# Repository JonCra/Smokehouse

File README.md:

# Project Smokehouse - RCET Project (Fall 2026 Semester)
## Continuation of [Project BLOODHOUND](https://github.com/rc-earnest/BloodHound)
### Smokehouse Contributors (Fall 2026 Semester)
<dl>
<dt>Micah Spencer - Project Lead, 6th Semester RCET Student</dt>
<dd>Redesign and improvement of drive controller(s) and addition of semi-permanent peripheral data collection</dd>
<dt>Jonas Cram - Project Lead, 6th Semester RCET Student</dt>
<dd>Design and construction of "control/base station" for remote operations</dd>
</dl>

### BLOODHOUND Contributors (Spring 2026 Semester)
<dl>
<dt>Noah Holloway - Project Lead, 6th Semester RCET Student</dt>
<dd>ATV steering/driving controls and physical/electrical hardware</dd>
<dt>Rudy Earnest - Project Lead, 6th Semester RCET Student</dt>
<dd>Pan-Tilt-Zoom (PTZ) Cameras and other peripherals</dd>
<dt>Micah Spencer - Project Assistant, 5th Semester RCET Student</dt>
<dd>Real-Time Kinematics (RTK)/GPS Module</dd>
<dt>Jonas Cram - Project Assistant, 5th Semester RCET Student</dt>
<dd>Light Detection and Ranging (LiDAR) Module</dd>

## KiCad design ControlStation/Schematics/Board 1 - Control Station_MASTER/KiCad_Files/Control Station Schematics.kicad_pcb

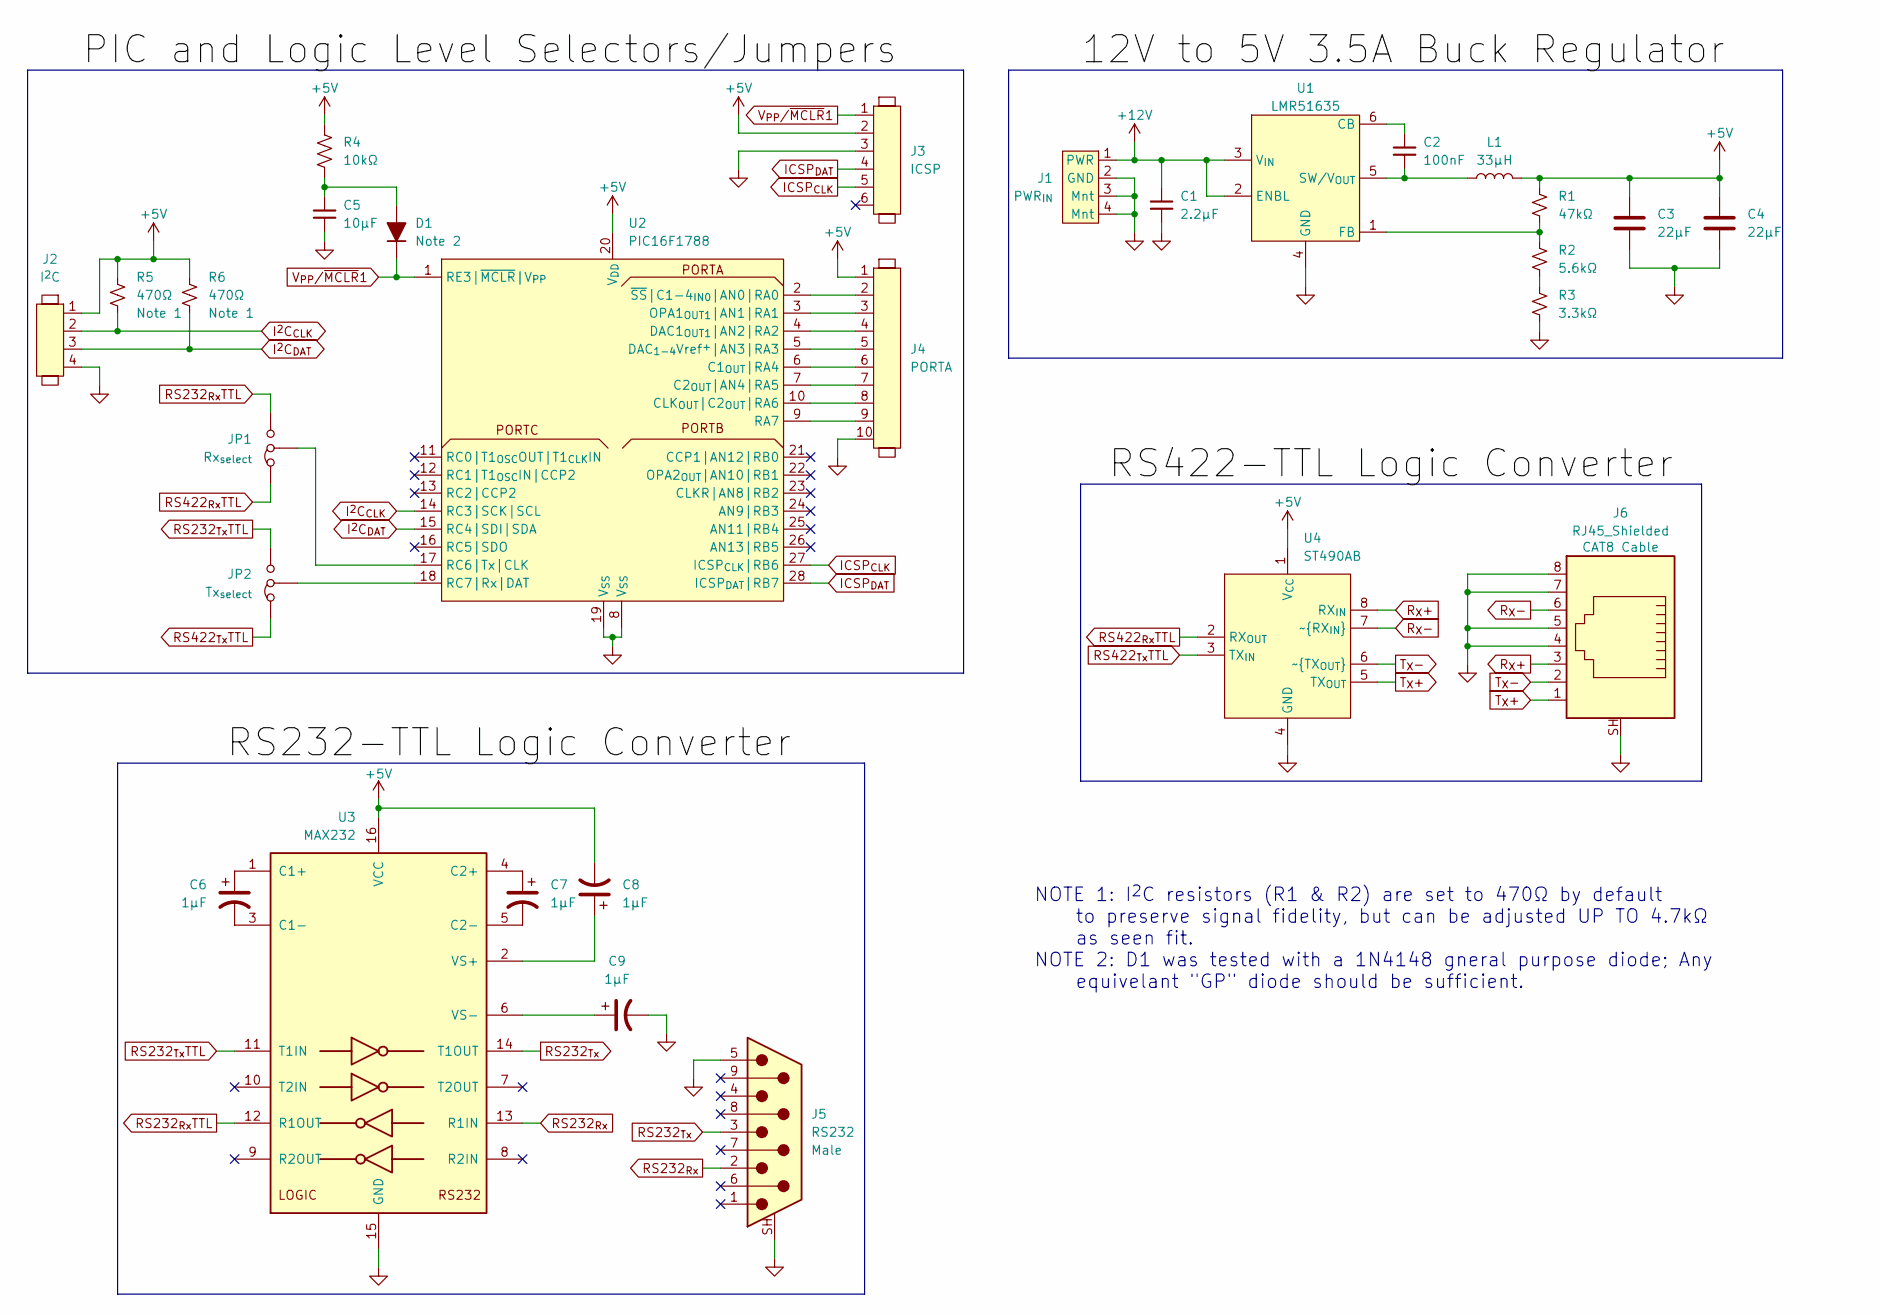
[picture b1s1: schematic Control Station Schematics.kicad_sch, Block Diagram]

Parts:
C1: 2.2μF; C_0805_2012Metric_Pad1.18x1.45mm_HandSolder
C2: 100nF; C_0805_2012Metric_Pad1.18x1.45mm_HandSolder
C3, C4: 22μF; C_0805_2012Metric_Pad1.18x1.45mm_HandSolder
C5: 10μF; C_0805_2012Metric_Pad1.18x1.45mm_HandSolder
C6, C7, C8, C9: 1μF; C_0805_2012Metric_Pad1.18x1.45mm_HandSolder
D1: D_0805_2012Metric_Pad1.15x1.40mm_HandSolder
J1: PWR_{IN}; XT30PW-M
J2: I^{2}C; Molex_Micro-Fit_3.0_43045-0400_2x02_P3.00mm_Horizontal
J3: ICSP; PinHeader_1x06_P1.00mm_Vertical
J4: PORTA; Molex_Micro-Fit_3.0_43045-1010_2x05-1MP_P3.00mm_Horizontal
J5: RS232; DSUB-9_Socket_Horizontal_P2.77x2.84mm_EdgePinOffset7.70mm_H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
J6: RJ45_Shielded; CONN8_406541_TEC
JP1: Rx_{select}; PinHeader_1x03_P1.00mm_Vertical
JP2: Tx_{select}; PinHeader_1x03_P1.00mm_Vertical
L1: 33μH; L_Bourns_SRP7028A_7.3x6.6mm
R1: 47kΩ; R_0805_2012Metric_Pad1.20x1.40mm_HandSolder
R2: 5.6kΩ; R_0805_2012Metric_Pad1.20x1.40mm_HandSolder
R3: 3.3kΩ; R_0805_2012Metric_Pad1.20x1.40mm_HandSolder
R4: 10kΩ; R_0805_2012Metric_Pad1.20x1.40mm_HandSolder
R5, R6: 470Ω; R_0805_2012Metric_Pad1.20x1.40mm_HandSolder
U1: LMR51635; DDC0006A-MFG
U2: PIC16F1788; SSOP-28
U3: MAX232; SOP-16_4.55x10.3mm_P1.27mm
U4: ST490AB; SO-8_3.9x4.9mm_P1.27mm

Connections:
+12V: C1.1, J1.1 (PWR), U1.2 (ENBL), U1.3 (V_{IN})
GND: C1.2, C3.2, C4.2, C5.2, C9.2, J1.2 (GND), J1.3 (Mnt), J1.4 (Mnt), J2.4, J3.3, J4.10, J5.5, J5.SH (PAD), J6.4, J6.5, J6.7, J6.8, J6.SH, R3.2, U1.4 (GND), U2.8 (V_{SS}), U2.19 (V_{SS}), U3.15 (GND), U4.4 (GND)
ICSP_{CLK}: J3.5, U2.27 (ICSP_{CLK}|RB6)
ICSP_{DAT}: J3.4, U2.28 (ICSP_{DAT}|RB7)
I^{2}C_{CLK}: J2.2, R5.2, U2.14 (RC3|SCK|SCL)
I^{2}C_{DAT}: J2.3, R6.2, U2.15 (RC4|SDI|SDA)
unnamed: C5.1, D1.2 (A), R4.2
unnamed: JP1.2 (C), U2.17 (RC6|Tx|CLK)
unnamed: JP2.2 (C), U2.18 (RC7|Rx|DAT)
unnamed: R2.2, R3.1
unnamed: C2.1, U1.6 (CB)
unnamed: R1.2, R2.1, U1.1 (FB)
unnamed: C2.2, L1.1, U1.5 (SW/V_{OUT})
unnamed: J4.6, U2.6 (C1_{OUT}|RA4)
unnamed: J4.7, U2.7 (C2_{OUT}|AN4|RA5)
unnamed: J4.8, U2.10 (CLK_{OUT}|C2_{OUT}|RA6)
unnamed: J4.4, U2.4 (DAC1_{OUT1}|AN2|RA2)
unnamed: J4.5, U2.5 (DAC_{1-4}Vref^{+}|AN3|RA3)
unnamed: J4.3, U2.3 (OPA1_{OUT1}|AN1|RA1)
unnamed: J4.9, U2.9 (RA7)
unnamed: J4.2, U2.2 (~SS|C1-4_{IN0}|AN0|RA0)
unnamed: C6.1, U3.1 (C1+)
unnamed: C6.2, U3.3 (C1-)
unnamed: C7.1, U3.4 (C2+)
unnamed: C7.2, U3.5 (C2-)
unnamed: C8.1, U3.2 (VS+)
unnamed: C9.1, U3.6 (VS-)
RS232_{Rx}: J5.2, U3.13 (R1IN)
RS232_{Rx}TTL: JP1.3 (B), U3.12 (R1OUT)
RS232_{Tx}: J5.3, U3.14 (T1OUT)
RS232_{Tx}TTL: JP2.3 (B), U3.11 (T1IN)
RS422_{Rx}TTL: JP1.1 (A), U4.2 (RX_{OUT})
RS422_{Tx}TTL: JP2.1 (A), U4.3 (TX_{IN})
R_{X}+: J6.3, U4.8 (RX_{IN})
R_{X}-: J6.6, U4.7 (~RX_{IN})
T_{X}+: J6.1, U4.5 (TX_{OUT})
T_{X}-: J6.2, U4.6 (~TX_{OUT})
V_{PP}/~MCLR1: D1.1 (K), J3.1, U2.1 (RE3|~MCLR|V_{PP})

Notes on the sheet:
NOTE 1: I^{2}C resistors (R1 & R2) are set to 470Ω by default to preserve signal fidelity, but can be adjusted UP TO 4.7kΩ as seen fit. NOTE 2: D1 was tested with a 1N4148 gneral purpose diode; Any equivelant "GP" diode should be sufficient.

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
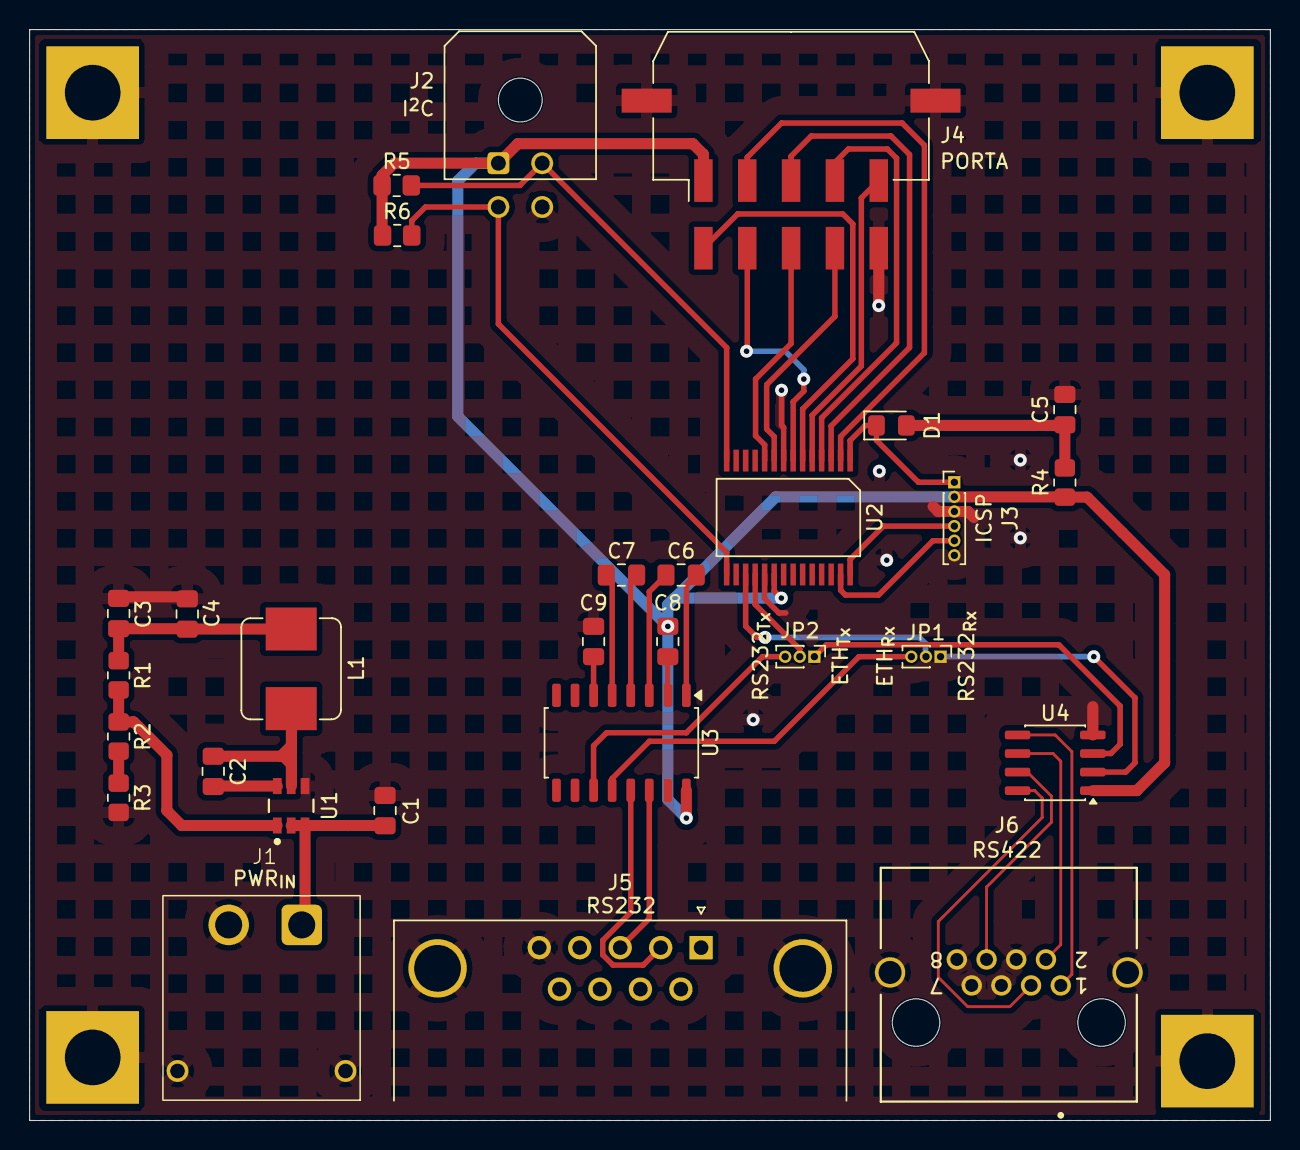
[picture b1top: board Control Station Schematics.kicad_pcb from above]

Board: 2 copper layers, 84.9 x 74.7 mm, 29 parts (0 on the bottom side), 40 nets.

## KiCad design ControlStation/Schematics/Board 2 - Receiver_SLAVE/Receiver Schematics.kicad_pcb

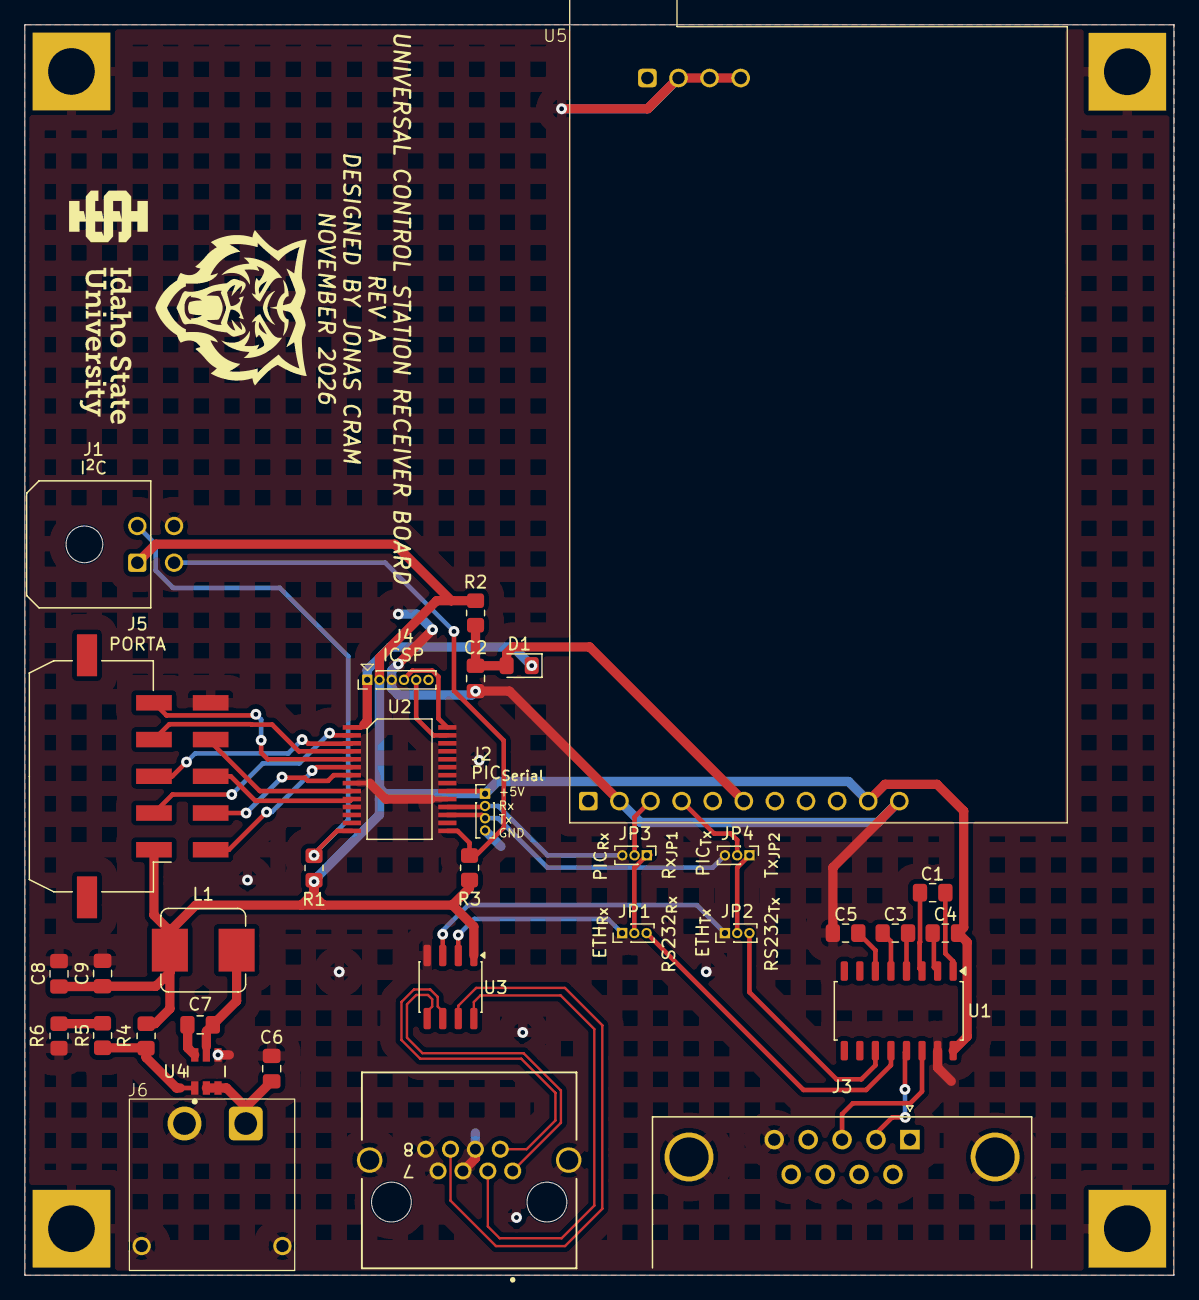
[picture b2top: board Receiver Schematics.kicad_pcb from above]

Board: 2 copper layers, 93.9 x 102.1 mm, 33 parts (0 on the bottom side), 43 nets.

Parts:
C1, C3, C4, C5: 1μF; C_0805_2012Metric_Pad1.18x1.45mm_HandSolder
C2: 10μF; C_0805_2012Metric_Pad1.18x1.45mm_HandSolder
C6: 2.2μF; C_0805_2012Metric_Pad1.18x1.45mm_HandSolder
C7: 100nF; C_0805_2012Metric_Pad1.18x1.45mm_HandSolder
C8, C9: 22μF; C_0805_2012Metric_Pad1.18x1.45mm_HandSolder
D1: Note 2; D_0805_2012Metric_Pad1.15x1.40mm_HandSolder
J1: I^{2}C; Molex_Micro-Fit_3.0_43045-0400_2x02_P3.00mm_Horizontal
J2: PIC_{Serial}; PinHeader_1x04_P1.00mm_Vertical
J3: RS232; DSUB-9_Socket_Horizontal_P2.77x2.84mm_EdgePinOffset7.70mm_H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
J4: ICSP; PinHeader_1x06_P1.00mm_Vertical
J5: PORTA; Molex_Micro-Fit_3.0_43045-1010_2x05-1MP_P3.00mm_Horizontal
J6: PWR_{IN}; XT30PW-M
J7: RJ45_Shielded; CONN8_406541_TEC
JP1: Rx_{select}1; PinHeader_1x03_P1.00mm_Vertical
JP2: Tx_{select}1; PinHeader_1x03_P1.00mm_Vertical
JP3: Rx_{select}2; PinHeader_1x03_P1.00mm_Vertical
JP4: Tx_{select}2; PinHeader_1x03_P1.00mm_Vertical
L1: 33μH; L_Bourns_SRP7028A_7.3x6.6mm
R1, R3: 470Ω; R_0805_2012Metric_Pad1.20x1.40mm_HandSolder
R2: 10kΩ; R_0805_2012Metric_Pad1.20x1.40mm_HandSolder
R4: 47kΩ; R_0805_2012Metric_Pad1.20x1.40mm_HandSolder
R5: 5.6kΩ; R_0805_2012Metric_Pad1.20x1.40mm_HandSolder
R6: 3.3kΩ; R_0805_2012Metric_Pad1.20x1.40mm_HandSolder
U1: MAX232; SOP-16_4.55x10.3mm_P1.27mm
U2: PIC16F1788; SSOP-28
U3: ST490AB; SO-8_3.9x4.9mm_P1.27mm
U4: LMR51635; DDC0006A-MFG
U5: 24XStream

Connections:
+5V: C4.2, C8.1, C9.1, J1.1, J2.1, J4.2, J5.1, L1.2, R1.1, R2.1, R3.1, R4.1, U1.16 (VCC), U2.20 (V_{DD}), U3.1 (V_{CC}), U5.10 (V_{CC})
+12V: C6.1, J6.1 (PWR), U4.2 (ENBL), U4.3 (V_{IN})
GND: C2.2, C5.2, C6.2, C8.2, C9.2, J1.4, J2.4, J3.5, J3.SH (PAD), J4.3, J5.10, J6.2 (GND), J6.3 (Mnt), J6.4 (Mnt), J7.4, J7.5, J7.7, J7.8, J7.SH, R6.2, U1.15 (GND), U2.8 (V_{SS}), U2.19 (V_{SS}), U3.4 (GND), U4.4 (GND), U5.2 (SLEEP), U5.11 (GND), U5.13 (2_{J2}), U5.14 (3_{J2}), U5.15 (4_{J2})
ICSP_{CLK}: J4.5, U2.27 (ICSP_{CLK}|RB6)
ICSP_{DAT}: J4.4, U2.28 (ICSP_{DAT}|RB7)
I^{2}C_{CLK}: J1.2, R1.2, U2.14 (RC3|SCK|SCL)
I^{2}C_{DAT}: J1.3, R3.2, U2.15 (RC4|SDI|SDA)
unnamed: JP1.2 (C), JP3.1 (A)
unnamed: JP2.2 (C), JP4.1 (A)
unnamed: JP3.2 (C), U5.3 (DATA_{OUT})
unnamed: JP4.2 (C), U5.4 (DATA_{IN})
unnamed: R5.2, R6.1
unnamed: C1.1, U1.1 (C1+)
unnamed: C1.2, U1.3 (C1-)
unnamed: C3.1, U1.4 (C2+)
unnamed: C3.2, U1.5 (C2-)
unnamed: C4.1, U1.2 (VS+)
unnamed: C5.1, U1.6 (VS-)
unnamed: J5.6, U2.6 (C1_{OUT}|RA4)
unnamed: J5.7, U2.7 (C2_{OUT}|AN4|RA5)
unnamed: J5.8, U2.10 (CLK_{OUT}|C2_{OUT}|RA6)
unnamed: J5.4, U2.4 (DAC1_{OUT1}|AN2|RA2)
unnamed: J5.5, U2.5 (DAC_{1-4}Vref^{+}|AN3|RA3)
unnamed: J5.3, U2.3 (OPA1_{OUT1}|AN1|RA1)
unnamed: J5.9, U2.9 (RA7)
unnamed: J5.2, U2.2 (~SS|C1-4_{IN0}|AN0|RA0)
unnamed: C7.1, U4.6 (CB)
unnamed: R4.2, R5.1, U4.1 (FB)
unnamed: C7.2, L1.1, U4.5 (SW/V_{OUT})
PIC_{Rx}: J2.2, JP3.3 (B), U2.18 (RC7|Rx|DAT)
PIC_{Tx}: J2.3, JP4.3 (B), U2.17 (RC6|Tx|CLK)
RS232_Rx_{TTL}: JP1.3 (B), U1.12 (R1OUT)
RS232_Tx_{TTL}: JP2.3 (B), U1.11 (T1IN)
RS232_{Rx}: J3.2, U1.13 (R1IN)
RS232_{Tx}: J3.3, U1.14 (T1OUT)
RS422_Rx_{TTL}: JP1.1 (A), U3.2 (RX_{OUT})
RS422_Tx_{TTL}: JP2.1 (A), U3.3 (TX_{IN})
R_{X}+: J7.3, U3.8 (RX_{IN})
R_{X}-: J7.6, U3.7 (~RX_{IN})
T_{X}+: J7.1, U3.5 (TX_{OUT})
T_{X}-: J7.2, U3.6 (~TX_{OUT})
V_{PP}/~MCLR: D1.1 (K), J4.1, U2.1 (RE3|~MCLR|V_{PP})
~POR: C2.1, D1.2 (A), R2.2, U5.6 (~RESET)
